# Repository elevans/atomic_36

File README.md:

# atomic_36
My take on a 36 key open source keyboard.

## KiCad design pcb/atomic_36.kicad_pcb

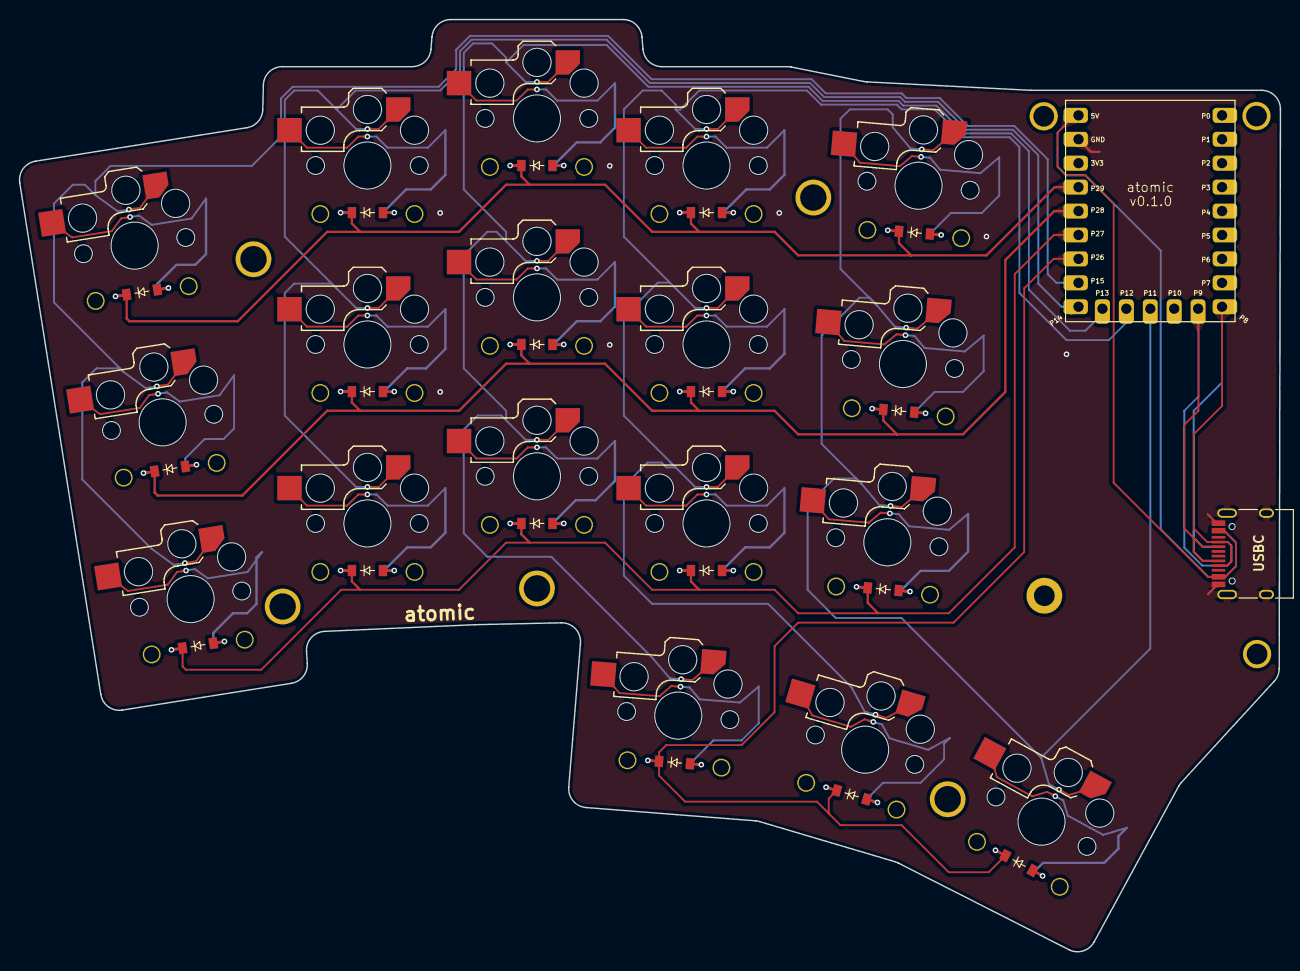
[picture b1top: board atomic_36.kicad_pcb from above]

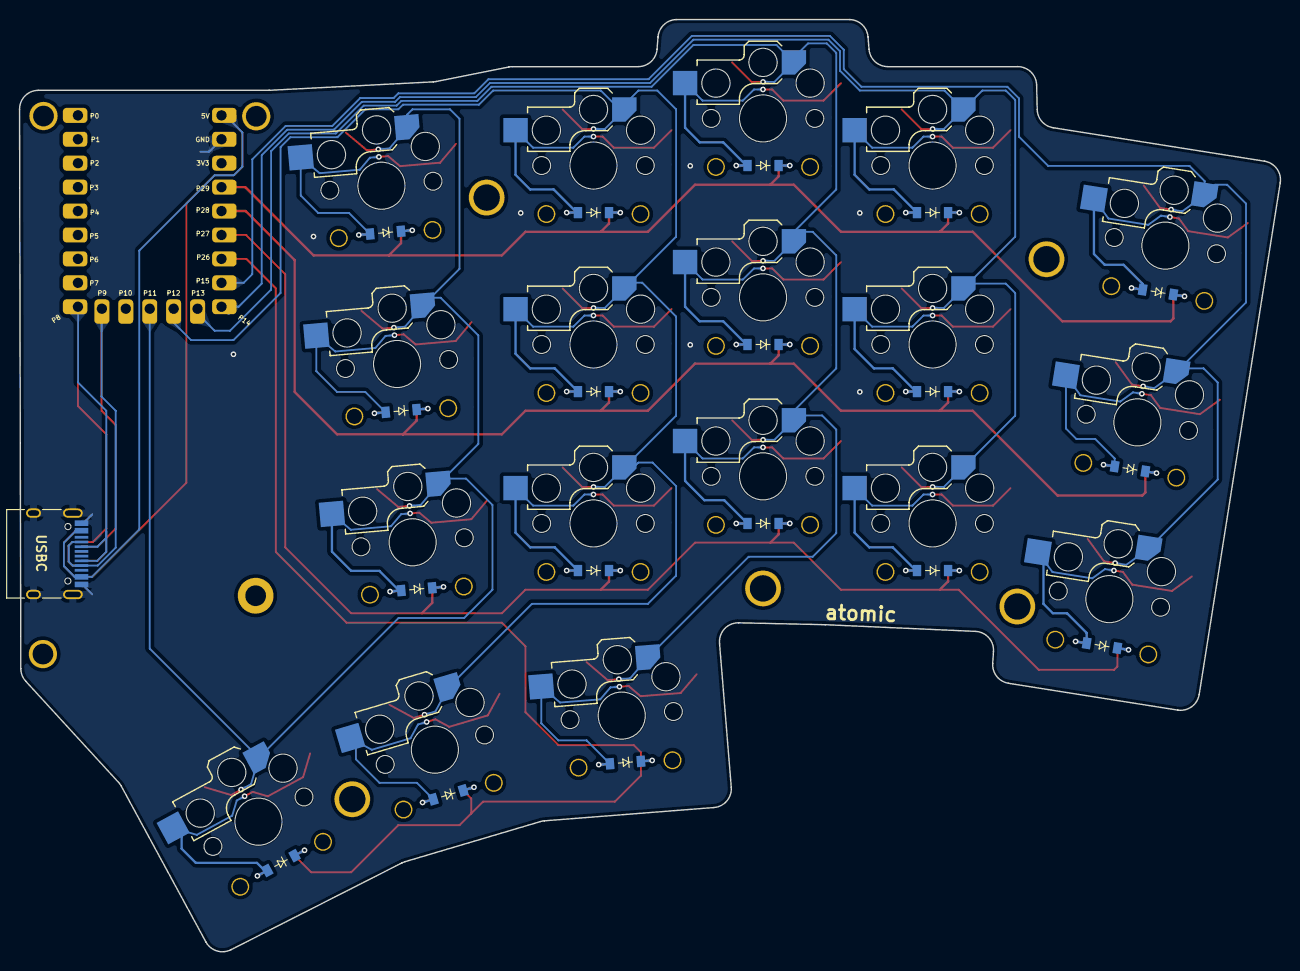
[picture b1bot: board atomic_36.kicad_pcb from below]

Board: 2 copper layers, 133.9 x 99.0 mm, 47 parts (18 on the bottom side), 31 nets.

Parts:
D1, D2, D3, D4, D5, D6, D7, D8, D9, D10, D11, D12, D13, D14, D15, D16, D17, D18: diode_tht_sod123
H1, H2, H3, H4, H5, H6, H7, H7#2, H9: mounting_hole_plated
J1: USB_C_12P; USB_C_Receptacle_HRO_TYPE-C-31-M-12_Reversible
RP2040Zero1: RP2040-Zero
S1, S2, S3, S4, S5, S6, S7, S8, S9, S10, S11, S12, S13, S14, S15, S16, S17, S18: switch_choc_v1_v2

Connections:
GND: J1.B1, J1.B12, J1.F1, J1.F12, J1.S1, RP2040Zero1.20
GP8: J1.B5, J1.B8, J1.F4, J1.F9, RP2040Zero1.9
GP9: J1.B4, J1.B9, J1.F5, J1.F8, RP2040Zero1.10
GP11: RP2040Zero1.12, S13.1, S14.1, S15.1, S18.1
GP12: RP2040Zero1.13, S10.1, S11.1, S12.1, S17.1
GP13: RP2040Zero1.14, S7.1, S8.1, S9.1, S16.1
GP14: RP2040Zero1.15, S4.1, S5.1, S6.1
GP15: RP2040Zero1.16, S1.1, S2.1, S3.1
GP26: D16.1, D17.1, D18.1, RP2040Zero1.17
GP27: D1.1, D4.1, D7.1, D10.1, D13.1, RP2040Zero1.18
GP28: D2.1, D5.1, D8.1, D11.1, D14.1, RP2040Zero1.22
GP29: D3.1, D6.1, D9.1, D12.1, D15.1, RP2040Zero1.23
P5V: J1.B2, J1.B11, J1.F2, J1.F11, RP2040Zero1.19
index_bottom: D10.2, S10.2
index_home: D11.2, S11.2
index_top: D12.2, S12.2
inner_bottom: D13.2, S13.2
inner_home: D14.2, S14.2
inner_top: D15.2, S15.2
layer_cluster: D17.2, S17.2
middle_bottom: D7.2, S7.2
middle_home: D8.2, S8.2
middle_top: D9.2, S9.2
mod_cluster: D16.2, S16.2
pinky_bottom: D1.2, S1.2
pinky_home: D2.2, S2.2
pinky_top: D3.2, S3.2
ring_bottom: D4.2, S4.2
ring_home: D5.2, S5.2
ring_top: D6.2, S6.2
space_cluster: D18.2, S18.2
